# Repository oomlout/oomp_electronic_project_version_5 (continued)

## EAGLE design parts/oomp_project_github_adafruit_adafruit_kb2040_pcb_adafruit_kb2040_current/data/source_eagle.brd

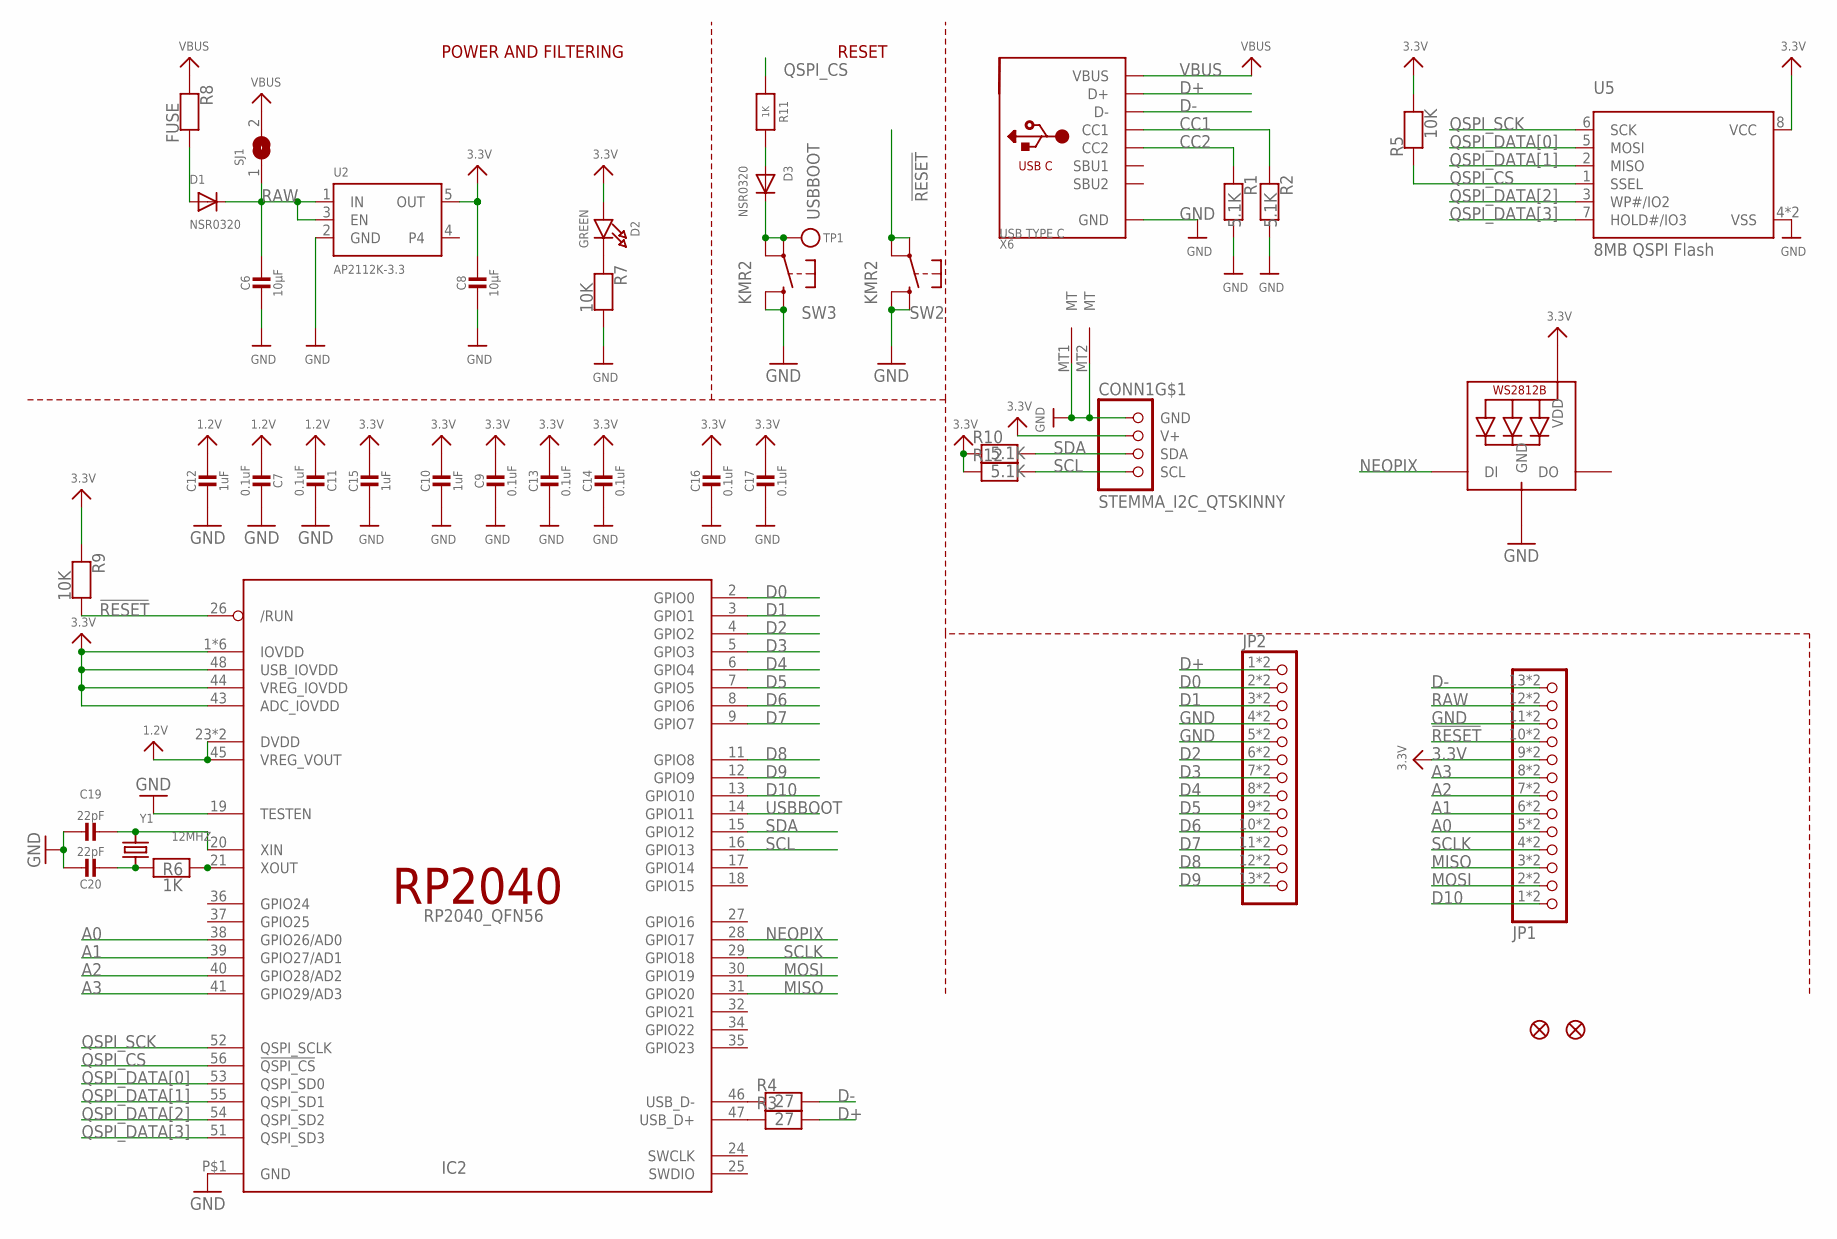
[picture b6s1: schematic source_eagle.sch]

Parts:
C6, C8: 10µF; _0805MP
C7, C9, C11, C13, C14, C16, C17: 0.1uF; _0402NO
C10, C12: 1uF; _0603MP
C15: 1uF; 0603-NO
C19, C20: 22pF; _0402NO
CONN1: STEMMA_I2C_QTSKINNY; JST_SH4_SKINNY
D1, D3: NSR0320; SOD-323F
D2: GREEN; CHIPLED_0603_NOOUTLINE
IC2: RP2040_QFN56; QFN56_7MM_REDUCEDEPAD
JP1, JP2: HEADER-1X13_CASTEL; 1X13_CASTEL
LED1: WS2812B_SK6805_1515; SK6805_1515
R1, R2, R10, R12: 5.1K; _0402NO
R3, R4: 27; _0402NO
R5, R7, R9: 10K; _0402NO
R6, R11: 1K; _0402NO
R8: FUSE; 0805-NO
SJ1: SOLDERJUMPER; SOLDERJUMPER_ARROW_NOPASTE
SW2, SW3: KMR2; BTN_KMR2_4.6X2.8
TP1: TESTPOINTROUND1.5MMNO; TESTPOINT_ROUND_1.5MM_NO
U2: AP2112K-3.3; SOT23-5
U5: 8MB QSPI Flash; USON8_4X4
U$34, U$35: FIDUCIAL_1MM
X6: USB TYPE C; USB_C_CUSB31-CFM2AX-01-X
Y1: 12MHZ; CRYSTAL_2.5X2

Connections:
1.2V: C7.2, C11.2, C12.1, IC2.23 (DVDD), IC2.45 (VREG_VOUT), IC2.50 (DVDD)
3.3V: C8.1, C9.1, C10.1, C13.1, C14.1, C15.1, C16.1, C17.1, CONN1.2 (V+), D2.A, IC2.1 (IOVDD), IC2.10 (IOVDD), IC2.22 (IOVDD), IC2.33 (IOVDD), IC2.42 (IOVDD), IC2.43 (ADC_IOVDD), IC2.44 (VREG_IOVDD), IC2.48 (USB_IOVDD), IC2.49 (IOVDD), JP1.9, JP1.9C (9), LED1.2 (VDD), R5.2, R9.1, R10.1, R12.1, U2.5 (OUT), U5.8 (VCC)
!RESET: IC2.26 (/RUN), JP1.10, JP1.10C (10), R9.2, SW2.A, SW2.A' (P1)
A0: IC2.38 (GPIO26/AD0), JP1.5, JP1.5C (5)
A1: IC2.39 (GPIO27/AD1), JP1.6, JP1.6C (6)
A2: IC2.40 (GPIO28/AD2), JP1.7, JP1.7C (7)
A3: IC2.41 (GPIO29/AD3), JP1.8, JP1.8C (8)
CC1: R2.1, X6.A5 (CC1)
CC2: R1.1, X6.B5 (CC2)
D0: IC2.2 (GPIO0), JP2.2, JP2.2C (2)
D1: IC2.3 (GPIO1), JP2.3, JP2.3C (3)
D2: IC2.4 (GPIO2), JP2.6, JP2.6C (6)
D3: IC2.5 (GPIO3), JP2.7, JP2.7C (7)
D4: IC2.6 (GPIO4), JP2.8, JP2.8C (8)
D5: IC2.7 (GPIO5), JP2.9, JP2.9C (9)
D6: IC2.8 (GPIO6), JP2.10, JP2.10C (10)
D7: IC2.9 (GPIO7), JP2.11, JP2.11C (11)
D8: IC2.11 (GPIO8), JP2.12, JP2.12C (12)
D9: IC2.12 (GPIO9), JP2.13, JP2.13C (13)
D10: IC2.13 (GPIO10), JP1.1, JP1.1C (1)
D+: JP2.1, JP2.1C (1), R3.2, X6.A6 (D+), X6.B6 (D+)
D-: JP1.13, JP1.13C (13), R4.2, X6.A7 (D-), X6.B7 (D-)
GND: C6.2, C7.1, C8.2, C9.2, C10.2, C11.1, C12.2, C13.2, C14.2, C15.2, C16.2, C17.2, C19.1, C20.1, CONN1.1 (GND), CONN1.MT1 (MT), CONN1.MT2 (MT), IC2.19 (TESTEN), IC2.P$1 (GND), JP1.11, JP1.11C (11), JP2.4, JP2.4C (4), JP2.5, JP2.5C (5), LED1.4 (GND), R1.2, R2.2, R7.2, SW2.B (S), SW2.B' (S1), SW3.B (S), SW3.B' (S1), U2.2 (GND), U5.4 (VSS), U5.PAD (VSS), X6.A1B12 (GND), X6.B1A12 (GND)
MISO: IC2.31 (GPIO20), JP1.3, JP1.3C (3)
MOSI: IC2.30 (GPIO19), JP1.2, JP1.2C (2)
unnamed: IC2.47 (USB_D+), R3.1
unnamed: D2.C, R7.1
unnamed: IC2.46 (USB_D-), R4.1
unnamed: D3.A, R11.2
unnamed: C19.2, IC2.20 (XIN), Y1.3 (2)
unnamed: C20.2, R6.1, Y1.1
unnamed: IC2.21 (XOUT), R6.2
unnamed: D1.A, R8.2
NEOPIX: IC2.28 (GPIO17), LED1.1 (DI)
QSPI_CS: IC2.56 (!QSPI_CS), R5.1, R11.1, U5.1 (SSEL)
QSPI_DATA[0]: IC2.53 (QSPI_SD0), U5.5 (MOSI)
QSPI_DATA[1]: IC2.55 (QSPI_SD1), U5.2 (MISO)
QSPI_DATA[2]: IC2.54 (QSPI_SD2), U5.3 (WP#/IO2)
QSPI_DATA[3]: IC2.51 (QSPI_SD3), U5.7 (HOLD#/IO3)
QSPI_SCK: IC2.52 (QSPI_SCLK), U5.6 (SCK)
RAW: C6.1, D1.C, JP1.12, JP1.12C (12), SJ1.1, U2.1 (IN), U2.3 (EN)
SCL: CONN1.4 (SCL), IC2.16 (GPIO13), R12.2
SCLK: IC2.29 (GPIO18), JP1.4, JP1.4C (4)
SDA: CONN1.3 (SDA), IC2.15 (GPIO12), R10.2
USBBOOT: D3.C, IC2.14 (GPIO11), SW3.A, SW3.A' (P1), TP1.P$1
VBUS: R8.1, SJ1.2, X6.A4B9 (VBUS), X6.B4A9 (VBUS)

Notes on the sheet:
POWER AND FILTERING
RESET

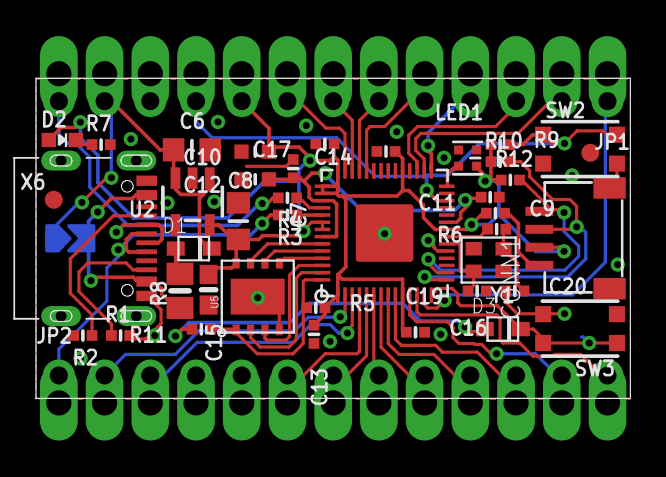
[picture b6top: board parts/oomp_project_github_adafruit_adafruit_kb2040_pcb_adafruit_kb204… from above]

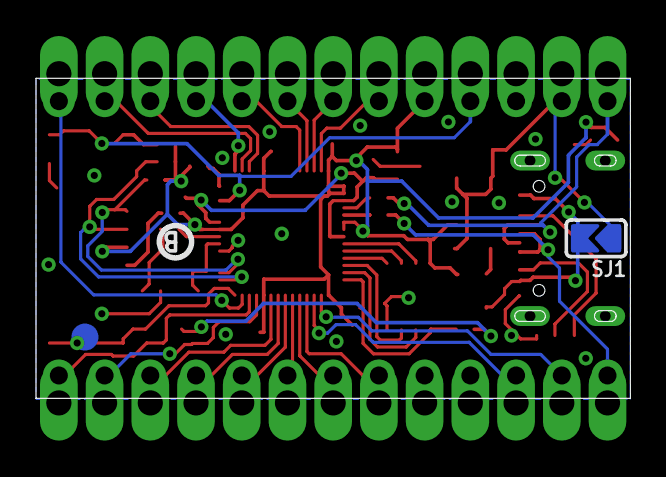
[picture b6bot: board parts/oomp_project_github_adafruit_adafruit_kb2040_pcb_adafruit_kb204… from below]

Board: 2 copper layers, 33.0 x 17.8 mm, 47 parts (4 on the bottom side), 46 nets.

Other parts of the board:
U$17: KB2040_BOT
U$19: KB2040_TOP
U$20: PCBFEAT-REV-040

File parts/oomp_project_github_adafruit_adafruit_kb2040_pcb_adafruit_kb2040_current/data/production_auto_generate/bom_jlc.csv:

Comment,Designator,Footprint,LCSC Part #
,"JP1,JP2",Adafruit KB2040-import-fps:1X13_CASTEL,C2894936
,U$17,Adafruit KB2040-import-fps:KB2040_BOT,
,U$19,Adafruit KB2040-import-fps:KB2040_TOP,
,U$20,Adafruit KB2040-import-fps:PCBFEAT-REV-040,
,TP1,Adafruit KB2040-import-fps:TESTPOINT_ROUND_1.5MM_NO,
0.1uF,"C7,C9,C11,C13,C14,C16,C17",Adafruit KB2040-import-fps:_0402NO,C60474
10K,"R5,R7,R9",Adafruit KB2040-import-fps:_0402NO,C2906861
10µF,"C6,C8",Adafruit KB2040-import-fps:_0805MP,
12MHZ,Y1,Adafruit KB2040-import-fps:CRYSTAL_2.5X2,
1K,"R6,R11",Adafruit KB2040-import-fps:_0402NO,C2906864
1uF,C15,Adafruit KB2040-import-fps:0603-NO,C5673
1uF,"C10,C12",Adafruit KB2040-import-fps:_0603MP,C5673
22pF,"C19,C20",Adafruit KB2040-import-fps:_0402NO,C106203
27,"R3,R4",Adafruit KB2040-import-fps:_0402NO,C25100
5.1K,"R1,R2,R10,R12",Adafruit KB2040-import-fps:_0402NO,C25905
8MB QSPI Flash,U5,Adafruit KB2040-import-fps:USON8_4X4,
AP2112K-3.3,U2,Adafruit KB2040-import-fps:SOT23-5,
FIDUCIAL_1MM,"U$34,U$35",Adafruit KB2040-import-fps:FIDUCIAL_1MM,
FUSE,R8,Adafruit KB2040-import-fps:0805-NO,
GREEN,D2,Adafruit KB2040-import-fps:CHIPLED_0603_NOOUTLINE,
KMR2,"SW2,SW3",Adafruit KB2040-import-fps:BTN_KMR2_4.6X2.8,
NSR0320,"D1,D3",Adafruit KB2040-import-fps:SOD-323F,
RP2040_QFN56,IC2,Adafruit KB2040-import-fps:QFN56_7MM_REDUCEDEPAD,
STEMMA_I2C_QTSKINNY,CONN1,Adafruit KB2040-import-fps:JST_SH4_SKINNY,
USB TYPE C,X6,Adafruit KB2040-import-fps:USB_C_CUSB31-CFM2AX-01-X,
WS2812B_SK6805_1515,LED1,Adafruit KB2040-import-fps:SK6805_1515,

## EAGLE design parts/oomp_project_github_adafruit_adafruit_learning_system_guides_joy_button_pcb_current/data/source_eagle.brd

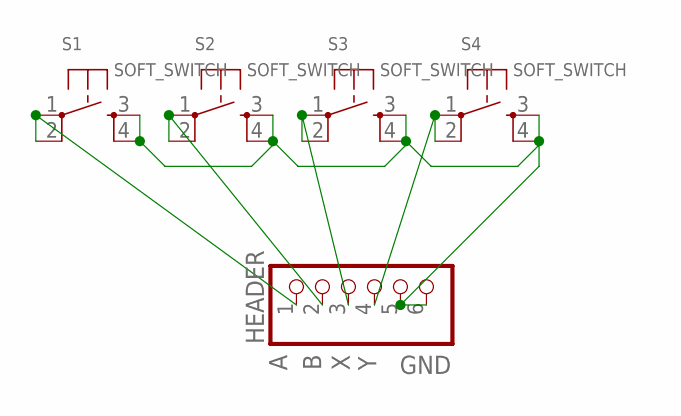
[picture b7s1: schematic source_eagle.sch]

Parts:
HEADER: PINHD-1X6; 1X06
S1, S2, S3, S4: SOFT_SWITCH; 8MM_SWITCH

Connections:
A: HEADER.1, S1.1, S1.2 (P1)
B: HEADER.2, S2.1, S2.2 (P1)
GND: HEADER.5, HEADER.6, S1.3 (S), S1.4 (S1), S2.3 (S), S2.4 (S1), S3.3 (S), S3.4 (S1), S4.3 (S), S4.4 (S1)
X: HEADER.3, S3.1, S3.2 (P1)
Y: HEADER.4, S4.1, S4.2 (P1)

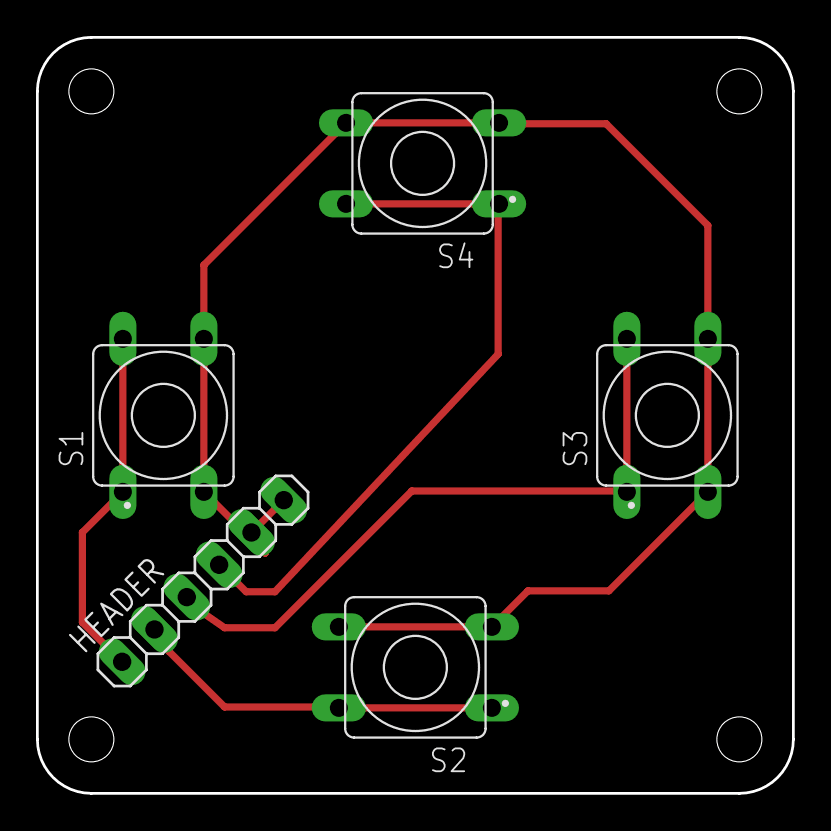
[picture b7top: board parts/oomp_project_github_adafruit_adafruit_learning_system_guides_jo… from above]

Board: 2 copper layers, 42.0 x 42.0 mm, 5 parts (0 on the bottom side), 5 nets.

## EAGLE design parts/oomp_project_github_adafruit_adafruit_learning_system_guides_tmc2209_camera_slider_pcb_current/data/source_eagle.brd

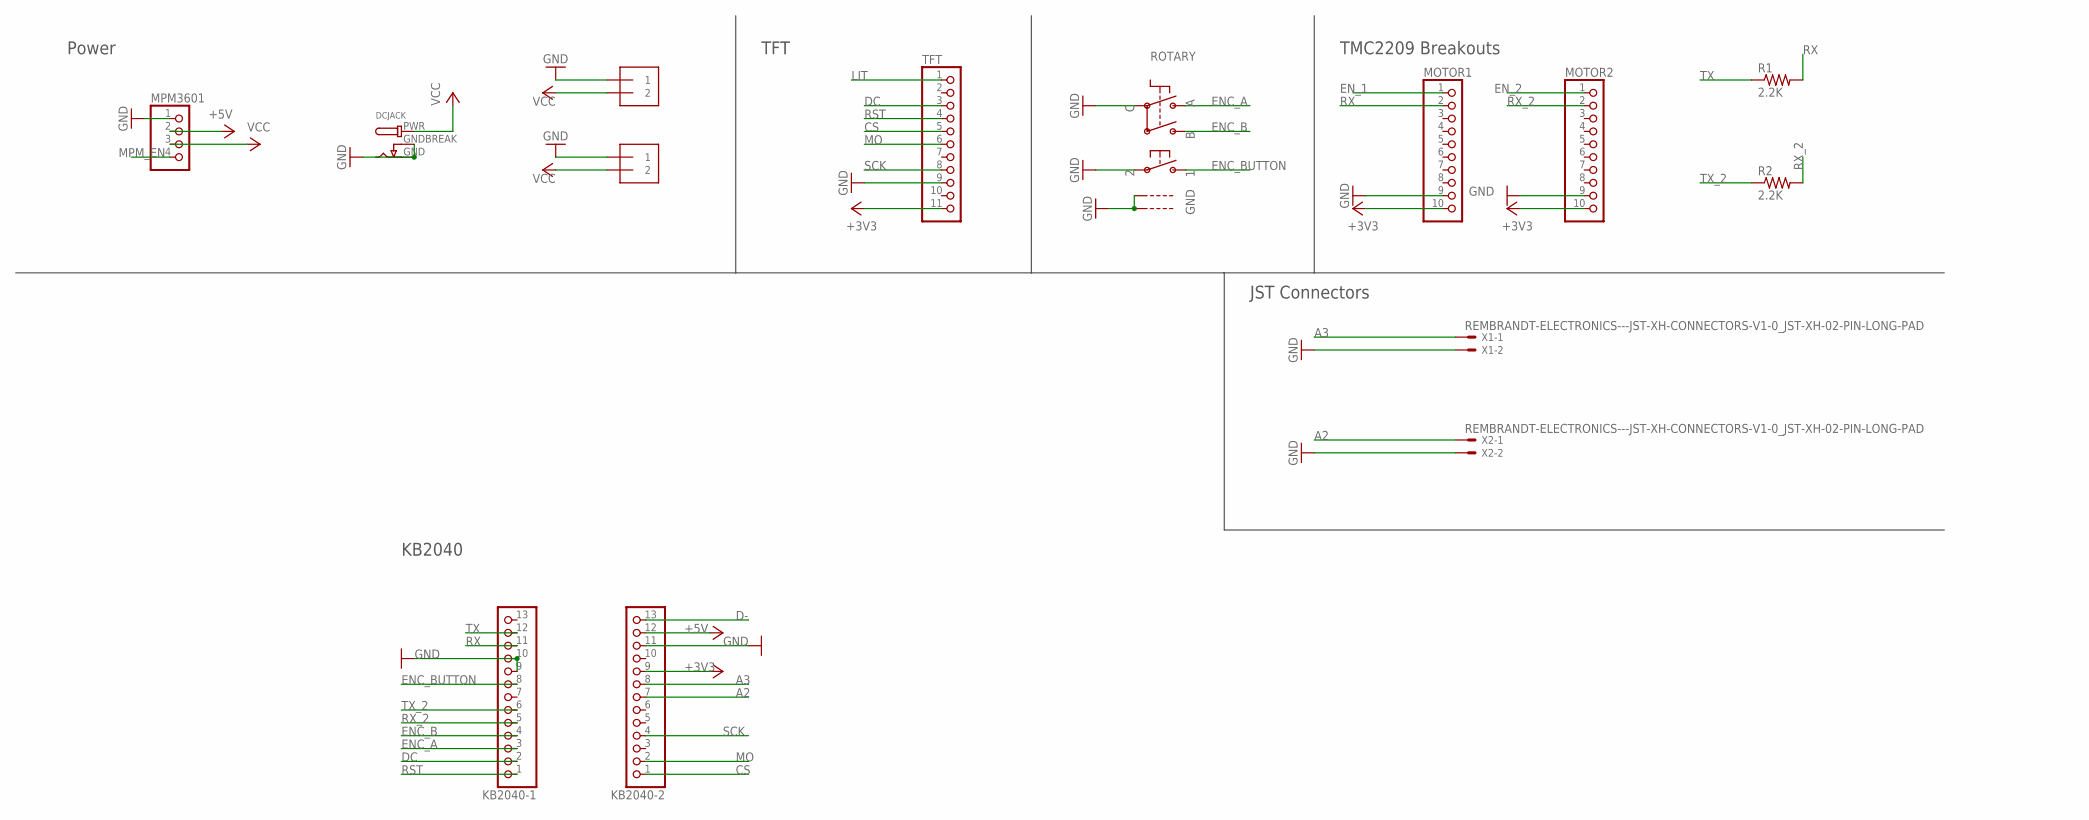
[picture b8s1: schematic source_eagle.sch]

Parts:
DCJACK: DCBARRELPTH; DCJACK_2MM_PTH
J1, J2: 1X2-3.5MM
KB2040-1, KB2040-2: HEADER-1X13; 1X13_ROUND_70
MOTOR1, MOTOR2: HEADER-1X10; 1X10_OVAL
MPM3601: HEADER-1X4; 1X04_OVAL
R1, R2: 2.2K; 0309/12
ROTARY: ENCODER_PLUS_SWITCH_BOURNS_PEC11; PEC11+SWITCH
TFT: HEADER-1X11; 1X11_ROUND
X1, X2: REMBRANDT-ELECTRONICS---JST-XH-CONNECTORS-V1-0_JS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; REMBRANDT-ELECTRONICS---JST-XH-CONNECTORS-V1-0_JST-XH-02-PA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

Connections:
+3V3: KB2040-2.9, MOTOR1.10, MOTOR2.10, TFT.11
+5V: KB2040-2.12, MPM3601.2
A2: KB2040-2.7, X2.1
A3: KB2040-2.8, X1.1
CS: KB2040-2.1, TFT.5
D-: KB2040-2.13
DC: KB2040-1.2, TFT.3
ENC_A: KB2040-1.3, ROTARY.P$A
ENC_B: KB2040-1.4, ROTARY.P$B
ENC_BUTTON: KB2040-1.8, ROTARY.P$1
EN_1: MOTOR1.1
EN_2: MOTOR2.1
GND: DCJACK.GND, DCJACK.GNDBREAK, J1.1, J2.1, KB2040-1.9, KB2040-1.10, KB2040-2.11, MOTOR1.9, MOTOR2.9, MPM3601.1, ROTARY.P$2, ROTARY.P$C, ROTARY.P$GND1, ROTARY.P$GND2, TFT.9, X1.2, X2.2
LIT: TFT.1
MO: KB2040-2.2, TFT.6
MPM_EN: MPM3601.4
RST: KB2040-1.1, TFT.4
RX: KB2040-1.11, MOTOR1.2, R1.2
RX_2: KB2040-1.5, MOTOR2.2, R2.2
SCK: KB2040-2.4, TFT.8
TX: KB2040-1.12, R1.1
TX_2: KB2040-1.6, R2.1
VCC: DCJACK.PWR, J1.2, J2.2, MPM3601.3

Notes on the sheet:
Power
TFT
TMC2209 Breakouts
KB2040
JST Connectors

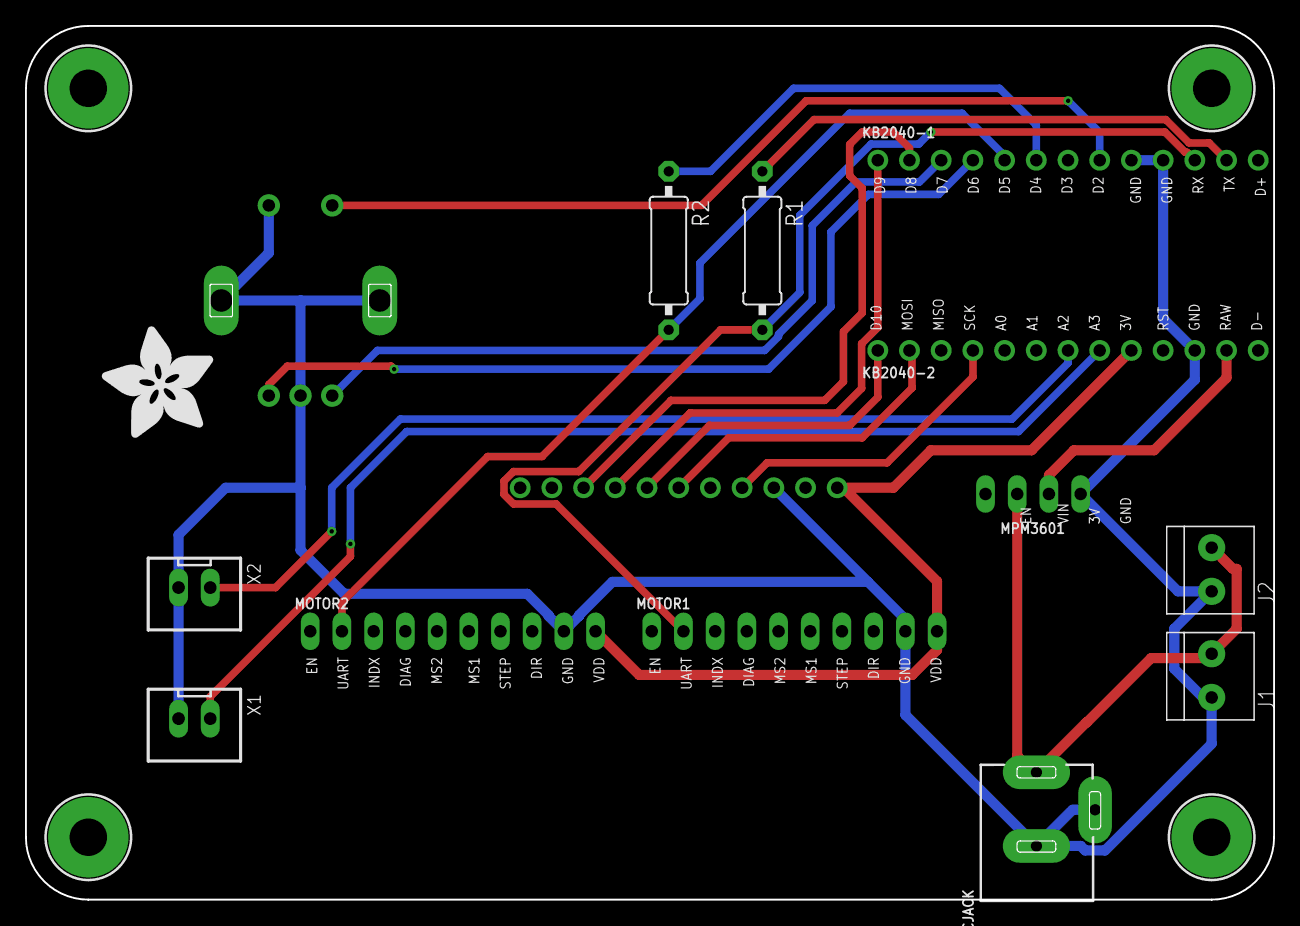
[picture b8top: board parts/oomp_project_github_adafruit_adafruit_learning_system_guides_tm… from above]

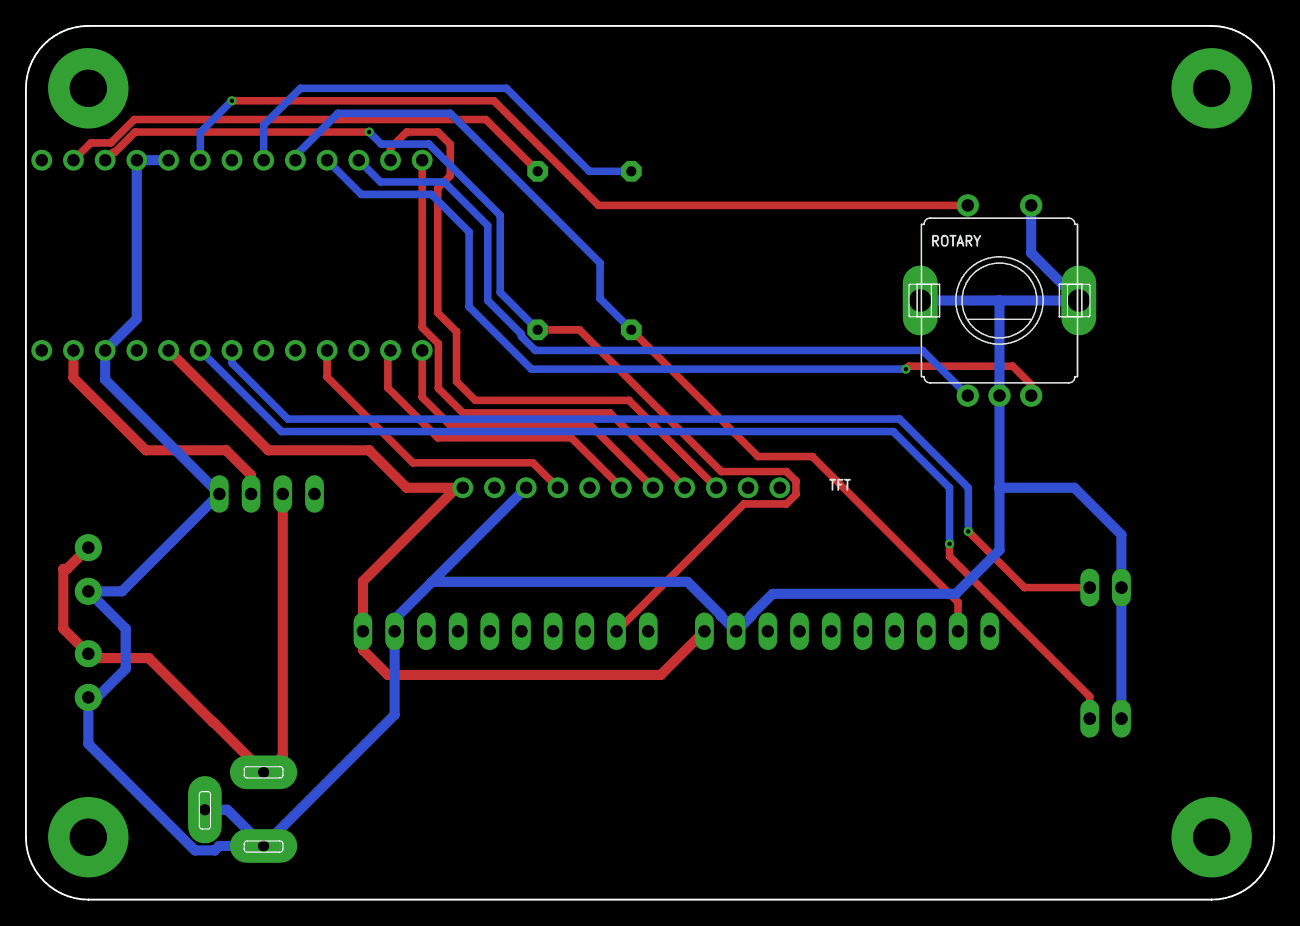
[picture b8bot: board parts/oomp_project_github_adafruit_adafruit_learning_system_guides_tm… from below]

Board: 2 copper layers, 100.0 x 70.0 mm, 114 parts (51 on the bottom side), 18 nets.

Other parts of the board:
E$1, E$2, E$3, E$5: MOUNTINGHOLE_3.0_PLATED
PLABEL0, PLABEL94: PLABEL0
PLABEL1, PLABEL6: PLABEL6
PLABEL2: PLABEL2
PLABEL3: PLABEL3
PLABEL4: PLABEL4
PLABEL5: PLABEL5
PLABEL7, PLABEL95: PLABEL1
PLABEL8: PLABEL8
PLABEL9: PLABEL9
PLABEL10: PLABEL10
PLABEL11: PLABEL11
PLABEL12: PLABEL12
PLABEL13: PLABEL13
PLABEL14: PLABEL14
PLABEL15: PLABEL15
PLABEL16, PLABEL96: PLABEL16
PLABEL17: PLABEL17
PLABEL18: PLABEL18
PLABEL19: PLABEL19
PLABEL21: PLABEL21
PLABEL24: PLABEL24
PLABEL25: PLABEL25
PLABEL26: PLABEL26
PLABEL27: PLABEL27
PLABEL28: PLABEL28
PLABEL29: PLABEL29
PLABEL30: PLABEL30
PLABEL31: PLABEL31
PLABEL32: PLABEL32
PLABEL33: PLABEL33
PLABEL34: PLABEL34
PLABEL35: PLABEL35
PLABEL36: PLABEL36
PLABEL41: PLABEL41
PLABEL42: PLABEL42
PLABEL43: PLABEL43
PLABEL44: PLABEL44
PLABEL45: PLABEL45
PLABEL46: PLABEL46
PLABEL47: PLABEL47
PLABEL48: PLABEL48
PLABEL49: PLABEL49
PLABEL50: PLABEL50
PLABEL51: PLABEL51
PLABEL52: PLABEL52
PLABEL53: PLABEL53
PLABEL54: PLABEL54
PLABEL55: PLABEL55
PLABEL56: PLABEL56
PLABEL57: PLABEL57
PLABEL58: PLABEL58
PLABEL59: PLABEL59
PLABEL60: PLABEL60
PLABEL61: PLABEL61
PLABEL62: PLABEL62
PLABEL63: PLABEL63
PLABEL64: PLABEL64
PLABEL65: PLABEL65
PLABEL66: PLABEL66
PLABEL67: PLABEL67
PLABEL68: PLABEL68
PLABEL69: PLABEL69
PLABEL70: PLABEL70
PLABEL71: PLABEL71
PLABEL72: PLABEL72
PLABEL73: PLABEL73
PLABEL74: PLABEL74
PLABEL75: PLABEL75
PLABEL76: PLABEL76
PLABEL77: PLABEL77
PLABEL78: PLABEL78
PLABEL79: PLABEL79
PLABEL80: PLABEL80
PLABEL81: PLABEL81
PLABEL82: PLABEL82
PLABEL83: PLABEL83
PLABEL84: PLABEL84
PLABEL85: PLABEL85
PLABEL86: PLABEL86
PLABEL87: PLABEL87
PLABEL88: PLABEL88
PLABEL89: PLABEL89
PLABEL90: PLABEL90
PLABEL91: PLABEL91
PLABEL92: PLABEL92
PLABEL93: PLABEL93
PLABEL200: PLABEL200
PLABEL201: PLABEL201
PLABEL202: PLABEL202
PLABEL203: PLABEL203
PLABEL204: PLABEL204
U$1: ADAFRUIT_9MM

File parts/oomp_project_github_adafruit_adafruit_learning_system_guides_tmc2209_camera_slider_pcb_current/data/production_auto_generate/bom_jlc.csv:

Comment,Designator,Footprint,LCSC Part #
,MPM3601,TMC2209_Camera_Slider_PCB_revB-import-fps:1X04_OVAL,C42431795
,"MOTOR1,MOTOR2",TMC2209_Camera_Slider_PCB_revB-import-fps:1X10_OVAL,C57369
,TFT0,TMC2209_Camera_Slider_PCB_revB-import-fps:1X11_ROUND,C2894934
,"KB2040-1,KB2040-2",TMC2209_Camera_Slider_PCB_revB-import-fps:1X13_ROUND_70,C2894936
,U$1,TMC2209_Camera_Slider_PCB_revB-import-fps:ADAFRUIT_9MM,
,DCJACK0,TMC2209_Camera_Slider_PCB_revB-import-fps:DCJACK_2MM_PTH,
,"PLABEL0,PLABEL94",TMC2209_Camera_Slider_PCB_revB-import-fps:PLABEL0,
,"PLABEL7,PLABEL95",TMC2209_Camera_Slider_PCB_revB-import-fps:PLABEL1,
,PLABEL10,TMC2209_Camera_Slider_PCB_revB-import-fps:PLABEL10,
,PLABEL11,TMC2209_Camera_Slider_PCB_revB-import-fps:PLABEL11,
,PLABEL12,TMC2209_Camera_Slider_PCB_revB-import-fps:PLABEL12,
,PLABEL13,TMC2209_Camera_Slider_PCB_revB-import-fps:PLABEL13,
,PLABEL14,TMC2209_Camera_Slider_PCB_revB-import-fps:PLABEL14,
,PLABEL15,TMC2209_Camera_Slider_PCB_revB-import-fps:PLABEL15,
,"PLABEL16,PLABEL96",TMC2209_Camera_Slider_PCB_revB-import-fps:PLABEL16,
,PLABEL17,TMC2209_Camera_Slider_PCB_revB-import-fps:PLABEL17,
,PLABEL18,TMC2209_Camera_Slider_PCB_revB-import-fps:PLABEL18,
,PLABEL19,TMC2209_Camera_Slider_PCB_revB-import-fps:PLABEL19,
,PLABEL2,TMC2209_Camera_Slider_PCB_revB-import-fps:PLABEL2,
,PLABEL200,TMC2209_Camera_Slider_PCB_revB-import-fps:PLABEL200,
,PLABEL201,TMC2209_Camera_Slider_PCB_revB-import-fps:PLABEL201,
,PLABEL202,TMC2209_Camera_Slider_PCB_revB-import-fps:PLABEL202,
,PLABEL203,TMC2209_Camera_Slider_PCB_revB-import-fps:PLABEL203,
,PLABEL204,TMC2209_Camera_Slider_PCB_revB-import-fps:PLABEL204,
,PLABEL21,TMC2209_Camera_Slider_PCB_revB-import-fps:PLABEL21,
,PLABEL24,TMC2209_Camera_Slider_PCB_revB-import-fps:PLABEL24,
,PLABEL25,TMC2209_Camera_Slider_PCB_revB-import-fps:PLABEL25,
,PLABEL26,TMC2209_Camera_Slider_PCB_revB-import-fps:PLABEL26,
,PLABEL27,TMC2209_Camera_Slider_PCB_revB-import-fps:PLABEL27,
,PLABEL28,TMC2209_Camera_Slider_PCB_revB-import-fps:PLABEL28,
,PLABEL29,TMC2209_Camera_Slider_PCB_revB-import-fps:PLABEL29,
,PLABEL3,TMC2209_Camera_Slider_PCB_revB-import-fps:PLABEL3,
,PLABEL30,TMC2209_Camera_Slider_PCB_revB-import-fps:PLABEL30,
,PLABEL31,TMC2209_Camera_Slider_PCB_revB-import-fps:PLABEL31,
,PLABEL32,TMC2209_Camera_Slider_PCB_revB-import-fps:PLABEL32,
,PLABEL33,TMC2209_Camera_Slider_PCB_revB-import-fps:PLABEL33,
,PLABEL34,TMC2209_Camera_Slider_PCB_revB-import-fps:PLABEL34,
,PLABEL35,TMC2209_Camera_Slider_PCB_revB-import-fps:PLABEL35,
,PLABEL36,TMC2209_Camera_Slider_PCB_revB-import-fps:PLABEL36,
,PLABEL4,TMC2209_Camera_Slider_PCB_revB-import-fps:PLABEL4,
,PLABEL41,TMC2209_Camera_Slider_PCB_revB-import-fps:PLABEL41,
,PLABEL42,TMC2209_Camera_Slider_PCB_revB-import-fps:PLABEL42,
,PLABEL43,TMC2209_Camera_Slider_PCB_revB-import-fps:PLABEL43,
,PLABEL44,TMC2209_Camera_Slider_PCB_revB-import-fps:PLABEL44,
,PLABEL45,TMC2209_Camera_Slider_PCB_revB-import-fps:PLABEL45,
,PLABEL46,TMC2209_Camera_Slider_PCB_revB-import-fps:PLABEL46,
,PLABEL47,TMC2209_Camera_Slider_PCB_revB-import-fps:PLABEL47,
,PLABEL48,TMC2209_Camera_Slider_PCB_revB-import-fps:PLABEL48,
,PLABEL49,TMC2209_Camera_Slider_PCB_revB-import-fps:PLABEL49,
,PLABEL5,TMC2209_Camera_Slider_PCB_revB-import-fps:PLABEL5,
,PLABEL50,TMC2209_Camera_Slider_PCB_revB-import-fps:PLABEL50,
,PLABEL51,TMC2209_Camera_Slider_PCB_revB-import-fps:PLABEL51,
,PLABEL52,TMC2209_Camera_Slider_PCB_revB-import-fps:PLABEL52,
,PLABEL53,TMC2209_Camera_Slider_PCB_revB-import-fps:PLABEL53,
,PLABEL54,TMC2209_Camera_Slider_PCB_revB-import-fps:PLABEL54,
,PLABEL55,TMC2209_Camera_Slider_PCB_revB-import-fps:PLABEL55,
,PLABEL56,TMC2209_Camera_Slider_PCB_revB-import-fps:PLABEL56,
,PLABEL57,TMC2209_Camera_Slider_PCB_revB-import-fps:PLABEL57,
,PLABEL58,TMC2209_Camera_Slider_PCB_revB-import-fps:PLABEL58,
,PLABEL59,TMC2209_Camera_Slider_PCB_revB-import-fps:PLABEL59,
,"PLABEL1,PLABEL6",TMC2209_Camera_Slider_PCB_revB-import-fps:PLABEL6,
,PLABEL60,TMC2209_Camera_Slider_PCB_revB-import-fps:PLABEL60,
,PLABEL61,TMC2209_Camera_Slider_PCB_revB-import-fps:PLABEL61,
,PLABEL62,TMC2209_Camera_Slider_PCB_revB-import-fps:PLABEL62,
,PLABEL63,TMC2209_Camera_Slider_PCB_revB-import-fps:PLABEL63,
,PLABEL64,TMC2209_Camera_Slider_PCB_revB-import-fps:PLABEL64,
,PLABEL65,TMC2209_Camera_Slider_PCB_revB-import-fps:PLABEL65,
,PLABEL66,TMC2209_Camera_Slider_PCB_revB-import-fps:PLABEL66,
,PLABEL67,TMC2209_Camera_Slider_PCB_revB-import-fps:PLABEL67,
,PLABEL68,TMC2209_Camera_Slider_PCB_revB-import-fps:PLABEL68,
,PLABEL69,TMC2209_Camera_Slider_PCB_revB-import-fps:PLABEL69,
,PLABEL70,TMC2209_Camera_Slider_PCB_revB-import-fps:PLABEL70,
,PLABEL71,TMC2209_Camera_Slider_PCB_revB-import-fps:PLABEL71,
,PLABEL72,TMC2209_Camera_Slider_PCB_revB-import-fps:PLABEL72,
,PLABEL73,TMC2209_Camera_Slider_PCB_revB-import-fps:PLABEL73,
,PLABEL74,TMC2209_Camera_Slider_PCB_revB-import-fps:PLABEL74,
,PLABEL75,TMC2209_Camera_Slider_PCB_revB-import-fps:PLABEL75,
,PLABEL76,TMC2209_Camera_Slider_PCB_revB-import-fps:PLABEL76,
,PLABEL77,TMC2209_Camera_Slider_PCB_revB-import-fps:PLABEL77,
,PLABEL78,TMC2209_Camera_Slider_PCB_revB-import-fps:PLABEL78,
,PLABEL79,TMC2209_Camera_Slider_PCB_revB-import-fps:PLABEL79,
,PLABEL8,TMC2209_Camera_Slider_PCB_revB-import-fps:PLABEL8,
,PLABEL80,TMC2209_Camera_Slider_PCB_revB-import-fps:PLABEL80,
,PLABEL81,TMC2209_Camera_Slider_PCB_revB-import-fps:PLABEL81,
,PLABEL82,TMC2209_Camera_Slider_PCB_revB-import-fps:PLABEL82,
,PLABEL83,TMC2209_Camera_Slider_PCB_revB-import-fps:PLABEL83,
,PLABEL84,TMC2209_Camera_Slider_PCB_revB-import-fps:PLABEL84,
,PLABEL85,TMC2209_Camera_Slider_PCB_revB-import-fps:PLABEL85,
,PLABEL86,TMC2209_Camera_Slider_PCB_revB-import-fps:PLABEL86,
,PLABEL87,TMC2209_Camera_Slider_PCB_revB-import-fps:PLABEL87,
,PLABEL88,TMC2209_Camera_Slider_PCB_revB-import-fps:PLABEL88,
,PLABEL89,TMC2209_Camera_Slider_PCB_revB-import-fps:PLABEL89,
,PLABEL9,TMC2209_Camera_Slider_PCB_revB-import-fps:PLABEL9,
,PLABEL90,TMC2209_Camera_Slider_PCB_revB-import-fps:PLABEL90,
,PLABEL91,TMC2209_Camera_Slider_PCB_revB-import-fps:PLABEL91,
,PLABEL92,TMC2209_Camera_Slider_PCB_revB-import-fps:PLABEL92,
,PLABEL93,TMC2209_Camera_Slider_PCB_revB-import-fps:PLABEL93,
1X2-3.5MM,"J1,J2",TMC2209_Camera_Slider_PCB_revB-import-fps:1X2-3.5MM,C492401
2.2K,"R1,R2",TMC2209_Camera_Slider_PCB_revB-import-fps:0309_12,
REMBRANDT-ELECTRONICS---JST-XH-CONNECTORS-V1-0_JST-XH-02-PIN-LONG-PAD,"X1,X2",TMC2209_Camera_Slider_PCB_revB-import-fps:REMBRANDT-ELECTRONICS---JST-XH-CONNECTORS-V1-0_JST-XH-02-PACKAGE-LONG-PAD,

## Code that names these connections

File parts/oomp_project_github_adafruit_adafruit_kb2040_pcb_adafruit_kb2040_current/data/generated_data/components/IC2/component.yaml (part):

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        pin_number: '8'
        pin_name: VCC
    - number: '2'
      name: GPIO0
      electrical_type: bidirectional
      graphic_style: line
      local_position:
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        pin_number: 2C
        pin_name: '2'
    - number: '3'
      name: GPIO1
      electrical_type: bidirectional
      graphic_style: line
      local_position:
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        pin_number: 3C
        pin_name: '3'
    - number: '4'
      name: GPIO2
      electrical_type: bidirectional
      graphic_style: line
      local_position:
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        pin_number: 6C
        pin_name: '6'
    - number: '5'
      name: GPIO3
      electrical_type: bidirectional
      graphic_style: line
      local_position:
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        pin_number: 7C
        pin_name: '7'
    - number: '6'
      name: GPIO4
      electrical_type: bidirectional
      graphic_style: line
      local_position:
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        pin_number: 8C
        pin_name: '8'
    - number: '7'
      name: GPIO5
      electrical_type: bidirectional
      graphic_style: line
      local_position:
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        pin_number: 9C
        pin_name: '9'
    - number: '8'
      name: GPIO6
      electrical_type: bidirectional
      graphic_style: line
      local_position:
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        pin_number: 10C
        pin_name: '10'
    - number: '9'
      name: GPIO7
      electrical_type: bidirectional
      graphic_style: line
      local_position:
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        pin_number: '8'
        pin_name: VCC
    - number: '11'
      name: GPIO8
      electrical_type: bidirectional
      graphic_style: line
      local_position:
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        pin_number: 12C
        pin_name: '12'
    - number: '12'
      name: GPIO9
      electrical_type: bidirectional
      graphic_style: line
      local_position:
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        pin_number: 13C
        pin_name: '13'
    - number: '13'
      name: GPIO10
      electrical_type: bidirectional
      graphic_style: line
      local_position:
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        pin_number: 1C
        pin_name: '1'
    - number: '14'
      name: GPIO11
      electrical_type: bidirectional
      graphic_style: line
      local_position:
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        pin_number: P$1
        pin_name: P$1
    - number: '15'
      name: GPIO12
      electrical_type: bidirectional
      graphic_style: line
      local_position:
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        pin_number: '2'
        pin_name: '2'
    - number: '16'
      name: GPIO13
      electrical_type: bidirectional
      graphic_style: line
      local_position:
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        pin_number: '2'
        pin_name: '2'
    - number: '17'
      name: GPIO14
      electrical_type: bidirectional
      graphic_style: line
      local_position:
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        pin_number: A'
        pin_name: P1
    - number: '27'
      name: GPIO16
      electrical_type: bidirectional
      graphic_style: line
      local_position:
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      no_connect: false
      connected_to: []
    - number: '28'
      name: GPIO17
      electrical_type: bidirectional
      graphic_style: line
      local_position:
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        pin_number: '1'
        pin_name: DI
    - number: '29'
      name: GPIO18
      electrical_type: bidirectional
      graphic_style: line
      local_position:
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        pin_number: 4C
        pin_name: '4'
    - number: '30'
      name: GPIO19
      electrical_type: bidirectional
      graphic_style: line
      local_position:
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        pin_number: 2C
        pin_name: '2'
    - number: '31'
      name: GPIO20
      electrical_type: bidirectional
      graphic_style: line
      local_position:
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      no_connect: false
      connected_to: []
    - number: '36'
      name: GPIO24
      electrical_type: bidirectional
      graphic_style: line
      local_position:
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      no_connect: false
      connected_to: []
    - number: '37'
      name: GPIO25
      electrical_type: bidirectional
      graphic_style: line
      local_position:
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      no_connect: false
      connected_to: []
    - number: '38'
      name: GPIO26/AD0
      electrical_type: bidirectional
      graphic_style: line
      local_position:
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        pin_number: 5C
        pin_name: '5'
    - number: '39'
      name: GPIO27/AD1
      electrical_type: bidirectional
      graphic_style: line
      local_position:
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        pin_number: 6C
        pin_name: '6'
    - number: '40'
      name: GPIO28/AD2
      electrical_type: bidirectional
      graphic_style: line
      local_position:
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        pin_number: 7C
        pin_name: '7'
    - number: '41'
      name: GPIO29/AD3
      electrical_type: bidirectional
      graphic_style: line
      local_position:
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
